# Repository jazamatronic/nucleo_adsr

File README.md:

# nucleo_adsr
STM32L432 based triple ADSR envelope generator

Very small sound demo with it in action [here](https://imgur.com/a/Ze2JWVJ)

ST generated files have their own license headers.

*NOTE* - R1, R5 and R9 should be 100k, not 2k as shown in the schematics.

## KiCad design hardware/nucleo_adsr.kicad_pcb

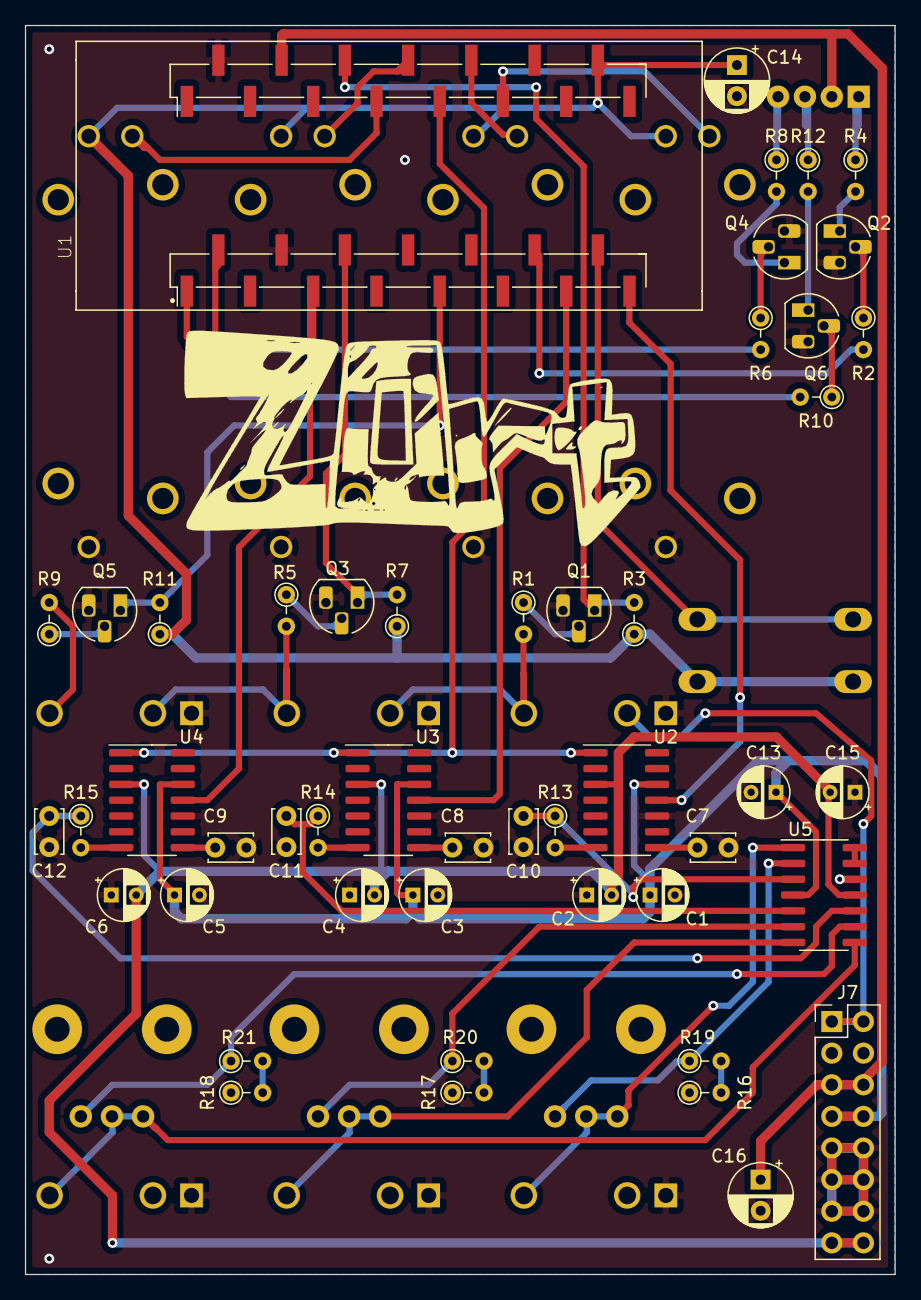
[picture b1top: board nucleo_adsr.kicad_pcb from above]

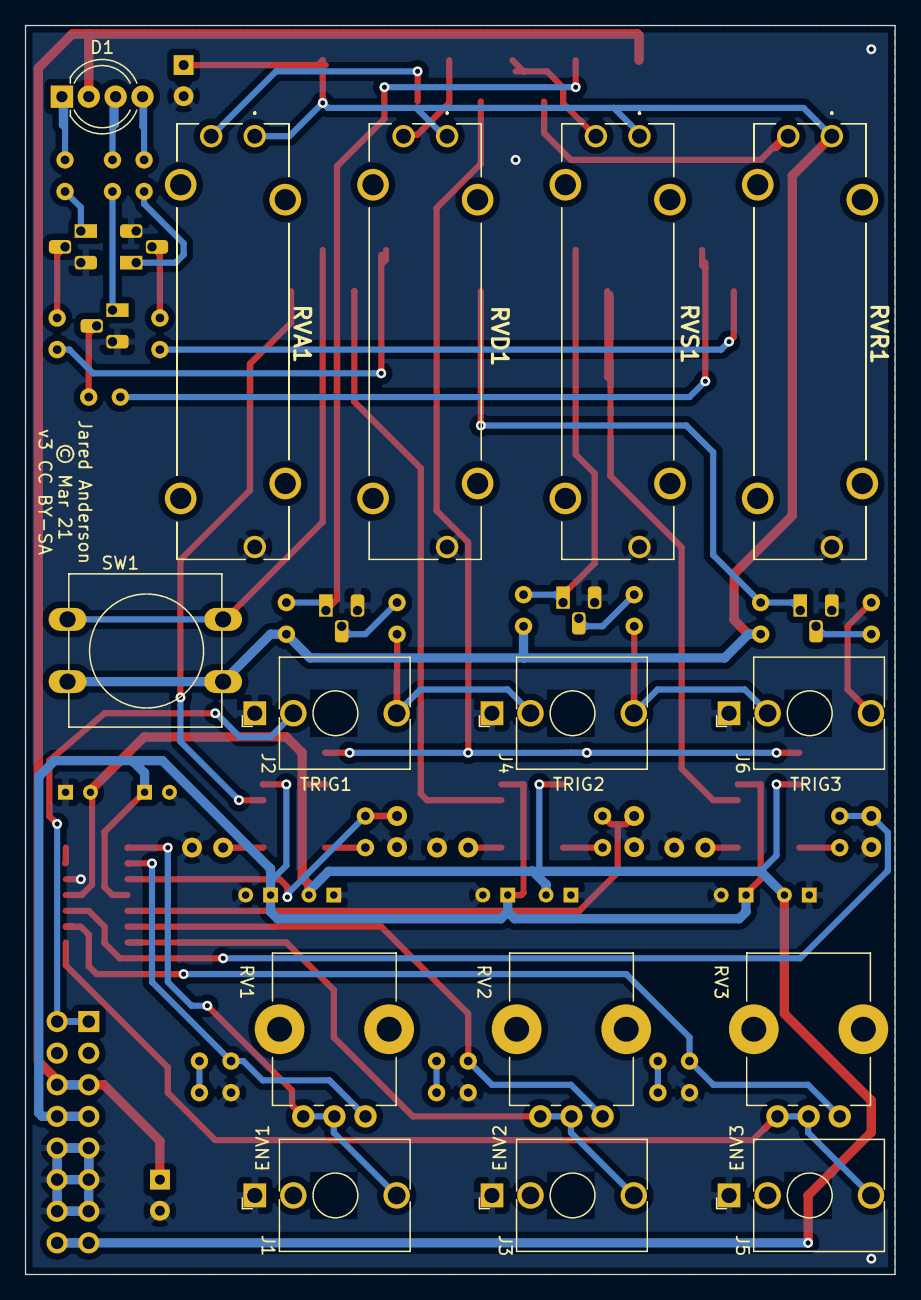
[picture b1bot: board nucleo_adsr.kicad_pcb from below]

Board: 2 copper layers, 69.8 x 100.3 mm, 64 parts (15 on the bottom side), 55 nets.

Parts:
C1, C2, C3, C4, C5, C6, C13, C15: 0.1u; CP_Radial_D4.0mm_P2.00mm
C7, C8, C9: 100p; C_Disc_D3.4mm_W2.1mm_P2.50mm
C10, C11, C12: 10n; C_Disc_D3.4mm_W2.1mm_P2.50mm
C14, C16: 10u; CP_Radial_D5.0mm_P2.50mm
D1: LED_RABG; LED_D5.0mm-4_RGB_Wide_Pins
J1: ENV1; Jack_3.5mm_QingPu_WQP-PJ398SM_Vertical_CircularHoles
J2: TRIG1; Jack_3.5mm_QingPu_WQP-PJ398SM_Vertical_CircularHoles
J3: ENV2; Jack_3.5mm_QingPu_WQP-PJ398SM_Vertical_CircularHoles
J4: TRIG2; Jack_3.5mm_QingPu_WQP-PJ398SM_Vertical_CircularHoles
J5: ENV3; Jack_3.5mm_QingPu_WQP-PJ398SM_Vertical_CircularHoles
J6: TRIG3; Jack_3.5mm_QingPu_WQP-PJ398SM_Vertical_CircularHoles
J7: PWR_HDR; PinHeader_2x08_P2.54mm_Vertical
Q1, Q2, Q3, Q4, Q5, Q6: BC547; TO-92_HandSolder
R1, R5, R9: 2k; R_Axial_DIN0204_L3.6mm_D1.6mm_P2.54mm_Vertical
R2, R6, R10: 1k; R_Axial_DIN0204_L3.6mm_D1.6mm_P2.54mm_Vertical
R3, R7, R11: 10k; R_Axial_DIN0204_L3.6mm_D1.6mm_P2.54mm_Vertical
R4, R8, R12: 4k7; R_Axial_DIN0204_L3.6mm_D1.6mm_P2.54mm_Vertical
R13, R14, R15: 100k; R_Axial_DIN0204_L3.6mm_D1.6mm_P2.54mm_Vertical
R16, R17, R18: 3k6; R_Axial_DIN0204_L3.6mm_D1.6mm_P2.54mm_Vertical
R19, R20, R21: 68k; R_Axial_DIN0204_L3.6mm_D1.6mm_P2.54mm_Vertical
RV1, RV2, RV3: 100k; Potentiometer_Bourns_PTV09A-1_Single_Vertical
RVA1: 100k; PTA20432010CIB103
RVD1: 100k; PTA20432010CIB103
RVR1: 100k; PTA20432010CIB103
RVS1: 100k; PTA20432010CIB103
SW1: SW_Push; SW_PUSH-12mm
U1: NUCLEO-L432KC; MODULE_NUCLEO-L432KC_SMT
U2, U3, U4: LF398_SOIC14; SOIC-14_3.9x8.7mm_P1.27mm
U5: TL074; SOIC-14_3.9x8.7mm_P1.27mm

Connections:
+3V3: C14.1, R3.1, R7.1, R11.1, RVA1.1, RVD1.1, RVR1.1, RVS1.1, SW1.2, U1.CN4_14
+5V: C16.1, D1.2, J7.5, J7.6, U1.CN4_4
+12V: C1.1, C3.1, C5.1, C13.1, J7.7, J7.8, U2.12, U3.12, U4.12, U5.4
-12V: C2.2, C4.2, C6.2, C15.2, J7.15, J7.16, U2.3, U3.3, U4.3, U5.11
ATTACK: RVA1.2, U1.CN4_11
BTN: SW1.1, U1.CN3_14
DAC_OUT: U1.CN4_9, U2.1, U3.1, U4.1
DECAY: RVD1.2, U1.CN4_10
ENV1: J1.T, RV1.2, RV1.3, U5.1
ENV2: J3.T, RV2.2, RV2.3, U5.7
ENV3: J5.T, RV3.2, RV3.3, U5.8
GATE: J2.TN, J7.1, J7.2
GND: C1.2, C2.1, C3.2, C4.1, C5.2, C6.1, C7.2, C8.2, C9.2, C10.2, C11.2, C12.2, C13.2, C14.2, C15.1, C16.2, J1.S, J2.S, J3.S, J4.S, J5.S, J6.S, J7.9, J7.10, J7.11, J7.12, J7.13, J7.14, Q1.3, Q2.3, Q3.3, Q4.3, Q5.3, Q6.3, R16.1, R17.1, R18.1, RVA1.3, RVD1.3, RVR1.3, RVS1.3, U1.CN3_4, U1.CN4_2, U2.10, U3.10, U4.10, U5.12
unnamed: C7.1, U2.8
unnamed: C8.1, U3.8
unnamed: C9.1, U4.8
unnamed: C10.1, R13.1, U5.3
unnamed: C11.1, R14.1, U5.5
unnamed: C12.1, R15.1, U5.10
unnamed: D1.1, R4.1
unnamed: D1.3, R12.1
unnamed: D1.4, R8.1
unnamed: Q1.2, R1.1
unnamed: Q2.1, R4.2
unnamed: Q2.2, R2.1
unnamed: Q3.2, R5.1
unnamed: Q4.1, R8.2
unnamed: Q4.2, R6.1
unnamed: Q5.2, R9.1
unnamed: Q6.1, R12.2
unnamed: Q6.2, R10.1
unnamed: R13.2, U2.7
unnamed: R14.2, U3.7
unnamed: R15.2, U4.7
unnamed: R16.2, R19.2
unnamed: R17.2, R20.2
unnamed: R18.2, R21.2
unnamed: R19.1, RV1.1, U5.2
unnamed: R20.1, RV2.1, U5.6
unnamed: R21.1, RV3.1, U5.9
unnamed: U5.13, U5.14
PWM_B: R10.2, U1.CN3_2
PWM_G: R6.2, U1.CN3_1
PWM_R: R2.2, U1.CN3_12
RELEASE: RVR1.2, U1.CN4_7
SH1: U1.CN3_15, U2.11
SH2: U1.CN3_13, U3.11
SH3: U1.CN3_5, U4.11
SUSTAIN: RVS1.2, U1.CN4_8
TRIG1: J2.T, J4.TN, R1.2
TRIG1_3V3: Q1.1, R3.2, U1.CN4_6
TRIG2: J4.T, J6.TN, R5.2
TRIG2_3V3: Q3.1, R7.2, U1.CN3_6
TRIG3: J6.T, R9.2
TRIG3_3V3: Q5.1, R11.2, U1.CN3_9

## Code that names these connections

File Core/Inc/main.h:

/* USER CODE BEGIN Header */
/**
  ******************************************************************************
  * @file           : main.h
  * @brief          : Header for main.c file.
  *                   This file contains the common defines of the application.
  ******************************************************************************
  * @attention
  *
  * <h2><center>&copy; Copyright (c) 2021 STMicroelectronics.
  * All rights reserved.</center></h2>
  *
  * This software component is licensed by ST under BSD 3-Clause license,
  * the "License"; You may not use this file except in compliance with the
  * License. You may obtain a copy of the License at:
  *                        opensource.org/licenses/BSD-3-Clause
  *
  ******************************************************************************
  */
/* USER CODE END Header */

/* Define to prevent recursive inclusion -------------------------------------*/
#ifndef __MAIN_H
#define __MAIN_H

#ifdef __cplusplus
extern "C" {
#endif

/* Includes ------------------------------------------------------------------*/
#include "stm32l4xx_hal.h"

/* Private includes ----------------------------------------------------------*/
/* USER CODE BEGIN Includes */

/* USER CODE END Includes */

/* Exported types ------------------------------------------------------------*/
/* USER CODE BEGIN ET */

/* USER CODE END ET */

/* Exported constants --------------------------------------------------------*/
/* USER CODE BEGIN EC */

/* USER CODE END EC */

/* Exported macro ------------------------------------------------------------*/
/* USER CODE BEGIN EM */

/* USER CODE END EM */

void HAL_TIM_MspPostInit(TIM_HandleTypeDef *htim);

/* Exported functions prototypes ---------------------------------------------*/
void Error_Handler(void);

/* USER CODE BEGIN EFP */

/* USER CODE END EFP */

/* Private defines -----------------------------------------------------------*/
#define TIM6_PSC 363
#define TIM6_PER 22
#define TIM1_PSC 4
#define TIM1_PER 8191
#define TIM7_PSC 79
#define SH_TIME 7
#define MCO_Pin GPIO_PIN_0
#define MCO_GPIO_Port GPIOA
#define ADC_A_Pin GPIO_PIN_1
#define ADC_A_GPIO_Port GPIOA
#define VCP_TX_Pin GPIO_PIN_2
#define VCP_TX_GPIO_Port GPIOA
#define ADC_D_Pin GPIO_PIN_3
#define ADC_D_GPIO_Port GPIOA
#define ADC_S_Pin GPIO_PIN_5
#define ADC_S_GPIO_Port GPIOA
#define ADC_R_Pin GPIO_PIN_6
#define ADC_R_GPIO_Port GPIOA
#define TRIG1_Pin GPIO_PIN_7
#define TRIG1_GPIO_Port GPIOA
#define TRIG2_Pin GPIO_PIN_0
#define TRIG2_GPIO_Port GPIOB
#define TRIG3_Pin GPIO_PIN_1
#define TRIG3_GPIO_Port GPIOB
#define PWM_R_Pin GPIO_PIN_8
#define PWM_R_GPIO_Port GPIOA
#define PWM_G_Pin GPIO_PIN_9
#define PWM_G_GPIO_Port GPIOA
#define PWM_B_Pin GPIO_PIN_10
#define PWM_B_GPIO_Port GPIOA
#define SH2_Pin GPIO_PIN_11
#define SH2_GPIO_Port GPIOA
#define SH3_Pin GPIO_PIN_12
#define SH3_GPIO_Port GPIOA
#define SWDIO_Pin GPIO_PIN_13
#define SWDIO_GPIO_Port GPIOA
#define SWCLK_Pin GPIO_PIN_14
#define SWCLK_GPIO_Port GPIOA
#define VCP_RX_Pin GPIO_PIN_15
#define VCP_RX_GPIO_Port GPIOA
#define LD3_Pin GPIO_PIN_3
#define LD3_GPIO_Port GPIOB
#define SH1_Pin GPIO_PIN_4
#define SH1_GPIO_Port GPIOB
#define BTN_Pin GPIO_PIN_5
#define BTN_GPIO_Port GPIOB
/* USER CODE BEGIN Private defines */

/* USER CODE END Private defines */

#ifdef __cplusplus
}
#endif

#endif /* __MAIN_H */

/************************ (C) COPYRIGHT STMicroelectronics *****END OF FILE****/

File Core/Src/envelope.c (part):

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void init_env(env_gen_t *env) {
  env->val = 0;
  env->mode = ONESHOT;
  env->adsr[ATTACK] = 0;
  env->adsr[DECAY] = 0;
  env->adsr[SUSTAIN] = 0;
  env->adsr[RELEASE] = 0;
  env->release_from = 0;
  env->triggered = 0;
  env->end = 0;
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
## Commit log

2021-03-21 Initial Import
2021-03-21 Update LICENSE
2021-05-12 Updated envelope timing so that a 0 value is twice that of the value calculated when it is 1
2022-02-11 Add parameter catching for the sliders. Update default segment shapes.
2022-02-12 Upgrade slider parameter catch to unlock once a parameter is caught.

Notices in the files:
Core/Src/envelope.c:
MIT License
Copyright (c) 2021 Jared Anderson
hardware/nucleo_adsr.kicad_pcb:
CC BY-SA
© Jared Anderson 2021
© Mar 21
v3 CC BY-SA
